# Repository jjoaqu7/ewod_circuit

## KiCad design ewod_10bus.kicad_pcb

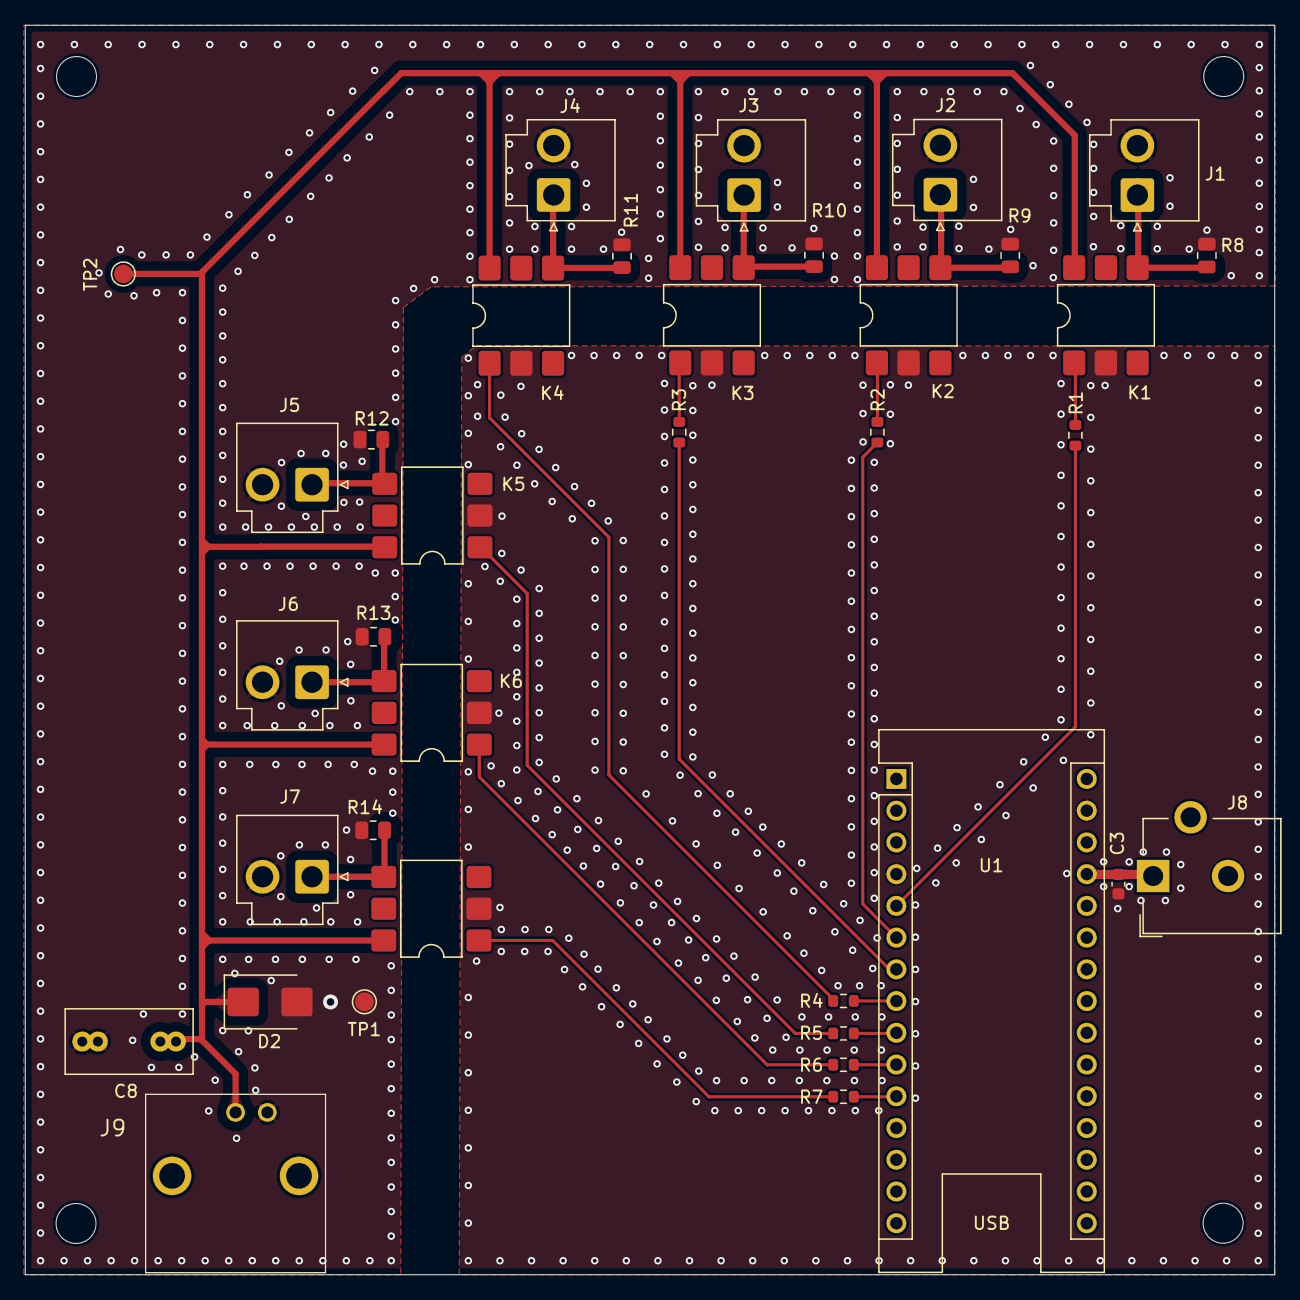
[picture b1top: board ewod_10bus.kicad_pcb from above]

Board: 2 copper layers, 100.0 x 100.0 mm, 36 parts (0 on the bottom side), 25 nets.

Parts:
C3: 100n; C_0603_1608Metric
C8: B32520E6104K000; C_Rect_L10.0mm_W5.0mm_P5.00mm_P7.50mm
D2: SMBJ200CA; D_SMB
J1, J2, J3, J4, J5, J6, J7: B2P-VH; JST_VH_B2P-VH-B_1x02_P3.96mm_Vertical
J8: Barrel_Jack; BarrelJack_CUI_PJ-102AH_Horizontal
J9: 031-5637; 0315637
K1, K2, K3, K4, K5, K6, K7: AQV254A; SMDIP-6_W7.62mm
R1, R2, R3, R4, R5, R6, R7: 1.2k; R_0603_1608Metric
R8, R9, R10, R11, R12, R13, R14: 1M; R_0805_2012Metric
TP1, TP2: TestPoint; TestPoint_Pad_D1.5mm
U1: Arduino_Nano_Every; Arduino_Nano

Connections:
/+5V: C3.1, J8.1, U1.27 (+5V)
/AMP_OUT: C8.2, D2.1, J9.2, K1.6 (D2), K2.6 (D2), K3.6 (D2), K4.6 (D2), K5.6 (D2), K6.6 (D2), K7.6 (D2), TP2.1
/BUS0_HV: J1.1, K1.4 (D1), R8.1
/BUS1_HV: J2.1, K2.4 (D1), R9.1
/BUS2_HV: J3.1, K3.4 (D1), R10.1
/BUS3_HV: J4.1, K4.4 (D1), R11.1
/BUS4_HV: J5.1, K5.4 (D1), R12.1
/BUS5_HV: J6.1, K6.4 (D1), R13.1
/BUS6_HV: J7.1, K7.4 (D1), R14.1
AMP_GND: C8.1, D2.2, J1.2, J2.2, J3.2, J4.2, J5.2, J6.2, J7.2, J9.1, R8.2, R9.2, R10.2, R11.2, R12.2, R13.2, R14.2, TP1.1
GND: C3.2, J8.2, K1.2 (K), K2.2 (K), K3.2 (K), K4.2 (K), K5.2 (K), K6.2 (K), K7.2 (K), U1.4 (GND), U1.29 (GND)
unnamed: K1.1 (A), R1.2
unnamed: K2.1 (A), R2.2
unnamed: K3.1 (A), R3.2
unnamed: K4.1 (A), R4.2
unnamed: K5.1 (A), R5.2
unnamed: K6.1 (A), R6.2
unnamed: K7.1 (A), R7.2
unnamed: R1.1, U1.5 (D2)
unnamed: R2.1, U1.6 (D3)
unnamed: R3.1, U1.7 (D4)
unnamed: R4.1, U1.8 (D5)
unnamed: R5.1, U1.9 (D6)
unnamed: R6.1, U1.10 (D7)
unnamed: R7.1, U1.11 (D8)

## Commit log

2025-06-29 first
2025-07-06 Update!
    - Added via shielding for signal integrity & EMC-related purposes.
    - Removed excessive decoupling capacitors.
    - Rerouted traces and slight repositioning to allow for shorter connections.
    - Added GND pour for both sides for better manufacturability and EMC-related performance.
2025-07-06 One More
2025-07-07 Update
    Adjusted spacing of output capacitor HV side.
